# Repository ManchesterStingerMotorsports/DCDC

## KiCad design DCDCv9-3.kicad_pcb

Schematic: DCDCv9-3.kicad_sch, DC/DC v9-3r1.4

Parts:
C1: 2uF; MKP1848520704K2; Mouser Part Number 75-MKP1848520704K2
C2: 2.2uF; C_0805_2012Metric; Manufacturer_Part_Number CL21B225KBYNNWE; not fitted
C3: 22nF; R76UI22205050J; Mouser Part Number 80-R76UI22205050J; not fitted
C4: 3.3nF; C_Disc_D12.5mm_W5.0mm_P10.00mm; Manufacturer_Part_Number VY1332M59Y5UQ63V0
C5, C33, C46: 10uF; C_0805_2012Metric; Manufacturer_Part_Number TMK212BBJ106KG-T
C8, C12, C18, C27, C42, C54: 22uF; C_0805_2012Metric; Manufacturer_Part_Number CL21A226MAYNNNE
C11, C13: 2200uF; CP_Radial_D12.5mm_P5.00mm_symbol_inside; Manufacturer_Part_Number UHW1V222MHD
C14, C28: 100nF; C_0603_1608Metric; Manufacturer_Part_Number HMJ107BB7104KAHT
C15, C40, C41: 2.2uF; C_0805_2012Metric; Manufacturer_Part_Number CL21B225KBYNNWE
C16, C49, C50, C51, C52, C53, C56, C57: 1nF; C_0603_1608Metric; Manufacturer_Part_Number 885342206003
C17, C19, C45: 1uF; C_0603_1608Metric; Manufacturer_Part_Number CL10B105KB8NQNC
C20, C21, C22, C23, C24: 10uF; C_1210_3225Metric; Manufacturer_Part_Number GRM32ER71J106MA12L
C26, C44, C47: 22nF; C_0603_1608Metric; Manufacturer_Part_Number C0603C223K1RAC
C29: 47pF; C_0603_1608Metric; Manufacturer_Part_Number C0603C470J1HACTU
C30, C32, C48: 10nF; C_0603_1608Metric; Manufacturer_Part_Number C0603C103K2RECTU
C34, C35, C36, C37: 5.6nF; C_1210_3225Metric; Manufacturer_Part_Number C1210C562JDGACAUTO
C38: 120pF; C_0603_1608Metric; Manufacturer_Part_Number GCM1885C2A121JA16D; not fitted
C39: 470pF; C_1206_3216Metric; Voltage 400V; Manufacturer_Part_Number 885342208005
C43: 470nF; C_0603_1608Metric; Manufacturer_Part_Number UMK107ABJ474KA-T
C_start1: 3.8V 25F Supercap; CP_Radial_D8.0mm_P3.50mm; Manufacturer_Part_Number VMF256M3R8
D1: HV_Orange; LED_0603_1608Metric_Pad1.05x0.95mm_HandSolder; Manufacturer_Part_Number APTD1608LSECK/J4-PF
D2, D10, D17, D18: 1N4448; D_SOD-123; Manufacturer_Part_Number 1N4448WQ-7-F
D3, D4, D5, D6, D7: Green; LED_0603_1608Metric_Pad1.05x0.95mm_HandSolder; Manufacturer_Part_Number IN-S63AT5G
D8, D15, D16: CDSOD323-T12; D_SOD-323; Manufacturer_Part_Number CDSOD323-T12
D9, D13: SS1H10; D_SMA; Manufacturer_Part_Number SS1H10-M3/61T
D11, D12, D14: VS-E7FX0212-M3/I; D_SMF; Manufacturer_Part_Number VS-E7FX0212-M3/I
F1: 1.6A; Fuseholder0,25Zoll_32mm_littlefuse_102_122; Manufacturer_Part_Number 0ADBC1600-BE
F1.1, F1.2: Manufacturer_Part_Number 01220083Z
F2: 500mA; NANO-0154-OMNI-BLOK-Fuse-Holder; Manufacturer_Part_Number 0154.500DR
F3: 20A; Bel_SMCF_Fuse_2410_6125Metric; Manufacturer_Part_Number 0679L9200-01
J2, J4, J8: Conn_01x02_Male; PinHeader_1x02_P2.54mm_Vertical; Manufacturer_Part_Number 42375-2486
J3, J6, J7: Molex Vert; Molex Microfit Vert
J9: Molex 3 pin; MPN 2165713003
JP1: Fan Voltage Select; SolderJumper-3_P1.3mm_Open_RoundedPad1.0x1.5mm_NumberLabels
L1: 4.7uH; ASPI-4030S; Mouser Part Number ASPI-4030S-4R7M-T
L2: 1uH; 7443091100_v9.2; Manufacturer_Part_Number 7443091100
L3: 10uH; ASPI-4030S; Mouser Part Number 815-ASPI-4030S-100MT
L4, L5, L6, L7, L8, L9, L10, L11: •
M1: Fan; PinHeader_1x02_P2.54mm_Vertical
Q1, Q2, Q5, Q6, Q7: PMV20ENR; SOT-23; Manufacturer_Part_Number PMV20ENR
Q3: SIHP24N80AE-GE3; TO-220-3_Vertical_HV1.2mm; Manufacturer_Part_Number SIHP24N80AE-GE3
Q4: IXYP8N90C3; TO-220-3_Vertical_HV1.2mm; Manufacturer_Part_Number IXYP8N90C3
Q10, Q11: IMBG65R050M2HXTMA1; TO-263-7_TabPin8; Manufacturer_Part_Number IMBG65R050M2HXTMA1
R1, R71: 100M; R_2512_6332Metric_Pad1.40x3.35mm_HandSolder; Manufacturer_Part_Number CHV2512-JW-107ELF
R2, R72: 330k; R_0805_2012Metric; Manufacturer_Part_Number ERJ-P06J334V
R3: 3.0k; R_0603_1608Metric; Manufacturer_Part_Number AF0603JR-073KL; not fitted
R4: 1k; R_0603_1608Metric; Manufacturer_Part_Number ESR03EZPJ102; not fitted
R5, R7, R9, R11, R15, R16, R21, R23, R51, R52, R55, R57, R63: 10k; R_0603_1608Metric; Manufacturer_Part_Number ESR03EZPJ103
R6: 47; R_1206_3216Metric; Manufacturer_Part_Number ERJ-P08J470V
R8, R10, R22, R48, R49: 2.2k; R_0603_1608Metric; Manufacturer_Part_Number ESR03EZPJ222
R12: 910; R_0603_1608Metric; Manufacturer_Part_Number CR0603-FX-9100ELF
R17, R24: 27k; R_0603_1608Metric; Manufacturer_Part_Number CR0603-JW-273ELF
R18, R27, R50: 470k; R_0603_1608Metric; Manufacturer_Part_Number RCS0603470KJNEA
R25: 240k; R_0603_1608Metric; Manufacturer_Part_Number AC0603FR-07240KL
R26, R45, R47, R53, R67, R70, R75: 100k; R_0603_1608Metric; Manufacturer_Part_Number ESR03EZPJ104
R28, R34, R66: 33k; R_0603_1608Metric; Manufacturer_Part_Number AC0603FR-0733KL
R31, R36: 4.7k; R_0603_1608Metric; Manufacturer_Part_Number CRCW06034K70FKEC
R35: 330k; R_0603_1608Metric; Manufacturer_Part_Number AC0603JR-07330KL
R37: 47k; R_0603_1608Metric; Manufacturer_Part_Number RC0603FR-0747KL
R39, R41, R59, R61: 1k; R_0603_1608Metric; Manufacturer_Part_Number ESR03EZPJ102
R44: 510; R_0603_1608Metric; Manufacturer_Part_Number CRCW0603510RFKEBC
R46: 20; R_1206_3216Metric; Manufacturer_Part_Number CR1206-FX-20R0ELF
R54: 10M; R_1206_3216Metric; Manufacturer_Part_Number CHV1206-JW-106ELF
R56, R58: 10; R_1206_3216Metric; Manufacturer_Part_Number RC1206FR-7W10RL
R60: 82k; R_0603_1608Metric; Manufacturer_Part_Number RC0603JR-0782KL
R62, R69: 100M; R_0603_1608Metric; Manufacturer_Part_Number CRCW0603100MJPEAHR
R64: 820k; R_0603_1608Metric; Manufacturer_Part_Number CR0603-FX-8203ELF
R65: 510k; R_0603_1608Metric; Manufacturer_Part_Number CR0603-JW-514ELF
R68: 1.6M; R_0603_1608Metric; Manufacturer_Part_Number AC0603FR-071M6L
R73, R74: 10; R_0603_1608Metric; Manufacturer_Part_Number ERJ-PA3J100V
RV1: 20k; Potentiometer_Bourns_PVG3G; Manufacturer_Part_Number PVG3A203C01R00
RV2: 10k; Potentiometer_Bourns_3214W_Vertical; Manufacturer_Part_Number PVG5A103C03R00
T1: DIY Transformer ETD 39; Transformer_ETD39_uprightV3.6 (PSS 24V); Manufacturer_Part_Number B66363G0000X197
T1.1: Ferrite Core; Manufacturer_Part_Number B66363G0000X197
T1.2: Ferrite Core (gapped); Manufacturer_Part_Number B66363G1000X127
T1.3: 1800 mm 120 x 0.1 mm HF litz wire (Prim); Manufacturer_Part_Number 120 x 0.1 mm
T1.4, T1.5: 165 mm 600 x 0,071 mm HF litz wire (inner Sec); Manufacturer_Part_Number 120 x 0.1 mm
TH1: 3.9k PTC (read build guide!); PinHeader_1x02_P2.54mm_Vertical; Manufacturer_Part_Number TFPTL15L3901FL2B
TH2: 1k PTC; R_0603_1608Metric; Manufacturer_Part_Number TFPT0603L1001DV
U1: RP-1212S; Converter_DCDC_TRACO_TBA 1-1212HI-3kV-iso; Manufacturer_Part_Number RP-1212S
U2: RT9058-90GVL; SOT-23; Manufacturer_Part_Number RT9058-90GVL
U3: MP4541_SOP8-EP; SOIC-8-1EP_3.9x4.9mm_P1.27mm_EP2.29x3mm XL7005; Manufacturer_Part_Number MP4541GN-Z
U4: TLV61048DBVR; SOT-23-6; Manufacturer_Part_Number TLV61048DBVR
U6, U10, U14: LM2904BIDDFR; SOT-23-8_DC-DC_v9; Manufacturer_Part_Number LM2904BIDDFR
U7: TL431BCDBZR; SOT-23; Manufacturer_Part_Number TL431BCDBZRG4
U9: ACPL-217-50AE; SOIC-4_4.55x2.6mm_P1.27mm; Manufacturer_Part_Number ACPL-217-560E
U11: UCC21520DW; SOIC-16W_7.5x10.3mm_P1.27mm; Manufacturer_Part_Number UCC21520DW
U12: UCC25600; SOIC-8_3.9x4.9mm_P1.27mm; Manufacturer_Part_Number UCC25600DR
U13: ZXRE330ASA-7; SOT-23; Manufacturer_Part_Number ZXRE330ASA-7

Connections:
24V_TP: C11.1, C13.1, C50.2, C51.2, C52.2, F2.1, F3.1, J4.1, L2.2, R17.1, R73.1, R74.1
+3V7: C8.1, C54.1, J3.2, JP1.3 (B), L1.1, U4.4 (~SHDN), U4.5 (IN), U4.6 (nc)
+9V: C5.1, C30.2, R39.1, U2.2 (VO), U9.1
+12V_HS: C41.2, D14.1 (K), U11.16 (VDDA)
+12V_IN: C2.2, C40.2, C45.2, C46.1, D2.1 (K), D3.2 (A), D4.2 (A), D11.1 (K), R70.1, U11.3 (VCCI), U11.8 (VCCI), U11.11 (VDDB), U12.7 (VCC), U14.8 (V+)
+12V_sw: C18.1, C19.2, C27.1, D9.1 (K), J8.1, JP1.1 (A), R16.1, R21.2, R27.1, R34.1, R35.2, R36.2, U1.1 (+VIN), U2.3 (VI), U6.8 (V+); also elsewhere on the board
+24V: C15.2, C53.2, F2.2, R26.2, U3.1 (EN), U3.8 (VIN)
+HV: C1.2, C34.1, C35.1, F1.2, Q11.8 (D), R1.1, R71.1, R72.1
+HV_in: F1.1, J9.3
-HV_in: C33.2, C38.1, D13.1 (K), J9.1, Q3.3 (S), R6.2, R7.2, R48.1, R50.1, R51.2, U1.5 (-VOUT), U10.4 (V-)
-HV_pc: C1.1, C3.2 (2_2), C4.1, C32.2, C36.2, C37.2, C43.2, C44.1, C45.1, C46.2, C47.2, D12.1 (K), D18.2 (A), Q1.2 (S), Q2.2 (S), Q3.2 (D), Q4.2 (C), Q10.3 (S), Q10.4 (S), Q10.5 (S), Q10.6 (S), Q10.7 (S), R2.2, R3.2, R5.1, R59.2, R60.1, R65.2, R68.2, RV1.3, RV2.2, RV2.3, U9.3, U11.4 (GND), U11.5 (DIS), U11.6 (DT), U12.6 (GND), U13.2, U14.4 (V-)
/HB_out: Q10.8 (D), Q11.3 (S), Q11.4 (S), Q11.5 (S), Q11.6 (S), Q11.7 (S), T1.1 (AA)
/HS: U11.1 (INA), U12.8 (GD1)
/LS: U11.2 (INB), U12.5 (GD2)
/OC: C44.2, D17.1 (K), R60.2, U12.3 (OC)
/OTP_FAN: Q5.1 (G), R18.1, U6.7
/OTP_OFF: D10.1 (K), Q6.1 (G), U6.1
/OVP: Q2.1 (G), R69.1, U14.7
/Opc+: C32.1, R44.2, U9.4
/Synchronous Rectification/3: T1.3 (SB); also elsewhere on the board
/Synchronous Rectification/5: T1.5 (SA); also elsewhere on the board
/UVP: Q1.1 (G), R62.1, R63.1, U14.1
GND: C4.2, C5.2, C8.2, C11.2, C12.1, C13.2, C15.1, C17.1, C18.2, C20.2, C21.2, C22.2, C23.2, C24.2, C27.2, C28.1, C48.1, C49.1, C50.1, C51.1, C52.1, C53.1, C54.2, C56.1, C57.1, C_start1.2 (-), D6.1 (K), D8.2 (A2), J4.2, J7.1, J7.2, Q5.2 (S), Q6.2 (S), R10.2, R11.2, R15.1, R22.1, R23.2, R25.1, R28.2, R31.1, R75.2, TH2.2, U2.1 (GND), U3.7 (GND), U4.2 (GND), U6.4 (V-), U7.3 (A); also elsewhere on the board
unnamed: C2.1, R4.2
unnamed: C26.2, R37.1
unnamed: C30.1, R41.1, U9.2
unnamed: C39.2, R54.1
unnamed: C42.2, R59.1
unnamed: C49.2, F3.2, J6.1, J6.2
unnamed: C56.2, R73.2
unnamed: C57.2, R74.2
unnamed: C_start1.1 (+), J3.1, Q7.3 (D)
unnamed: D1.2 (A), R72.2
unnamed: D1.1 (K), R2.1
unnamed: C47.1, D2.2 (A), R67.2, R71.2, U14.2 (-)
unnamed: D3.1 (K), R63.2
unnamed: D4.1 (K), R5.2
unnamed: D5.2 (A), R9.1
unnamed: D5.1 (K), R7.1, R8.2, U10.7
unnamed: D6.2 (A), R21.1
unnamed: C12.2, C16.2, D7.2 (A), L3.2, Q7.2 (S), R24.1
unnamed: D7.1 (K), R22.2
unnamed: D8.1 (A1), Q7.1 (G), R26.1
unnamed: D9.2 (A), L1.2, U4.1 (SW)
unnamed: C48.2, D10.2 (A), R11.1, R34.2, U6.3 (+)
unnamed: C33.1, D11.2 (A), R9.2, R45.2, R46.2, R47.2, R53.2, U1.7 (+VOUT), U10.8 (V+)
unnamed: D12.2 (A), R52.1
unnamed: D13.2 (A), Q4.3 (E), R6.1, U10.2 (-)
unnamed: D14.2 (A), R46.1
unnamed: D15.1 (A1), Q10.1 (G), R55.1, R56.1
unnamed: C40.1, D15.2 (A2), Q10.2 (DS), R55.2, U11.9 (VSSB)
unnamed: D16.1 (A1), Q11.1 (G), R57.1, R58.1
unnamed: C41.1, D16.2 (A2), Q11.2 (DS), R57.2, U11.14 (VSSA)
unnamed: C39.1, D17.2 (A), D18.1 (K)
unnamed: J2.1, JP1.2 (C)
unnamed: J2.2, Q5.3 (D)
unnamed: C19.1, J8.2, R31.2, R75.1, U6.6 (-)
unnamed: L4.2, L5.1
unnamed: L6.1, L7.2
unnamed: L8.1, L9.1
unnamed: L10.1, L11.2
unnamed: Q1.3 (D), Q2.3 (D), R61.1
unnamed: Q3.1 (G), R8.1
unnamed: Q4.1 (G), R49.1
unnamed: R10.1, R12.2
unnamed: R49.2, R51.1, U10.1
unnamed: R65.1, R66.2
unnamed: R67.1, R68.1
unnamed: C34.2, C35.2, C36.1, C37.1, R54.2, T1.2 (AB)
unnamed: C20.1, C21.1, C22.1, C23.1, C24.1, L2.1, T1.4 (SC)
unnamed: C14.2, U3.5 (BST)
unnamed: C16.1, R23.1, R24.2, U3.4 (FB)
unnamed: R25.2, U3.3 (FREQU)
unnamed: C14.1, L3.1, U3.6 (SW)
unnamed: C17.2, U3.2 (VCC)
unnamed: R27.2, R28.1, U4.3 (FB)
unnamed: C28.2, R35.1, R36.1, TH2.1, U6.2 (-)
unnamed: R15.2, R16.2, R18.2, U6.5 (+)
unnamed: C29.2, R37.2, R39.2, R41.2, U7.1 (K)
unnamed: C26.1, C29.1, R12.1, R17.2, U7.2 (REF)
unnamed: R45.1, R48.2, U10.3 (+)
unnamed: R47.1, R50.2, U10.5 (+)
unnamed: C38.2, R52.2, R53.1, U10.6 (-)
unnamed: R58.2, U11.15 (OUTA)
unnamed: R56.2, U11.10 (OUTB)
unnamed: R3.1, R4.1, RV1.1, RV1.2, U12.1 (DT)
unnamed: C42.1, R44.1, RV2.1, U12.2 (RT)
unnamed: C43.1, R61.2, U12.4 (SS)
unnamed: R62.2, R64.1, U14.3 (+)
unnamed: R1.2, R66.1, R69.2, U14.5 (+)
unnamed: R64.2, R70.2, U13.1, U14.6 (-)
OTP_FET: Q6.3 (D), U1.2 (-VIN)

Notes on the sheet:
2.79V
PWM ramp-up hack via dead time (not working!) when C2+R4 is installed with 10 uF and 1k somehow the soft start does not work properly. It starts from 127 kHz and goes down to 95 kHz (normal). When C2 is not installed, Soft start starts from 341 kHz (nice!)
3.3 V (constant)
f_max
OVP Voltages: 100 Meg + 543 k Measured 241127: Enable: 609V / Disable 598V -> OK
Calculation is not up-to date, as R75 (100k) was added on 250619 R54 = 470k U_on = 5.9466 V = 4784.4 Ω = 1.2267 = 77 °C U_off = 6.0533 V = 4617.2 Ω = 1.1839 = 68 °C 106.7 mV hysteresis
between 2.5V and 3.8V (depending on SOC) ESR: 0,65 Ω (DC), 0,3Ω (1kHz AC)
If the MP4541 is not available, use the MP4581 (1:1 compatible, 100V variant)
500mW
FB Voltage: 1.0 V V_out = 1.0 * (1+ R_24/R_23) V_out = 1.0 * (1+ 27k/10k) = 3.7 V Note: 3.7 V is used for some safty margin to the allowed 3.8 V of the Supercap.
HV DC in
UVP
Cr_B
CC precharge IGBT
C3 is a hidden footprint for a film capacitor on the PCB as backup solution in case of a Cr_A / Cr_B failure. If needed, pin 1 must be connected with a short cable to T1 pin 2. If C3 is used, P_out must not exceed 500W !
Lp = 166 µH Lr = 56 µH
The UVP/OVP signals pull down the soft start capacitor, and force the UCC25600 to turn off. When UVP/OVP are OK (low), the soft start capacitor is recharged, while a sweep from high frequency to lower (normal) frequency is output, resulting in a soft start of the half-bridge. RT is also LOW when SS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
470 nF - UCC25600 Tool Softstart: 265ms
R_dT
f_min
precharge-close MOS
Placed near U2
SOT23-5 Footprint was adapted to SOT23-6 (mostly cross compatible) Works for: - TLV61048DBVR, 3.7 A, FB-Voltage: 0.8 V (best efficieny), 600 kHz, 2 ms softstart, U_in_min 2.65 (RECOMMENDED, USED HERE) - MT3608, 2 A, FB-Voltage: 0.6 V (often found in cheap Amazon Boost converters), 1200 kHz, U_in_mi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
Mount TH1 on the outsiede of the transformer. NOT INSIDE FOOTPRINT J8!
local bypass for U12
Glossary OCP over current protection UVP under voltage protectin PC precharge ref reference (voltage) sw manually switched switch/connector/source HV high voltage opc optocoupler opamp operational amplifier pwr power dashed line modul/sub module dash-dotted line optional part, see comment
DC/DC enable Switch
TH2 is next to SR FETs
OVP
p_max = 3.3 W @ 600 V
Split resonant capacitors result in half the Current per cap and a DC_link_cap capacity reduction by appx. 3.5x (same Voltage ripple). Not more than 2 Arms per side are expected at 400V / 500W load. However, it's better having 2 in parallel, bc I dont like seeing burning C0G caps (again).
2.5*(1+((27)/(2.2+0.91))) = 24.2042 V
Overtemperature Protection and Fan control
current sensing shunt I_pc = 5.5 mA
|__________| = 4634.0 Ω
V_curr_sens
V_ref = 258 mV
11.7k = 300ns
Active Center tapped Full-Wave Rectifier
UCC21520 A bypass capacitor connected to VCCI supports the transient current needed for the primary logic and the total current consumption, which is only a few mA. Therefore, a 50-V MLCC with over 100 nF is recommended for this application. -> See Datasheet for further information

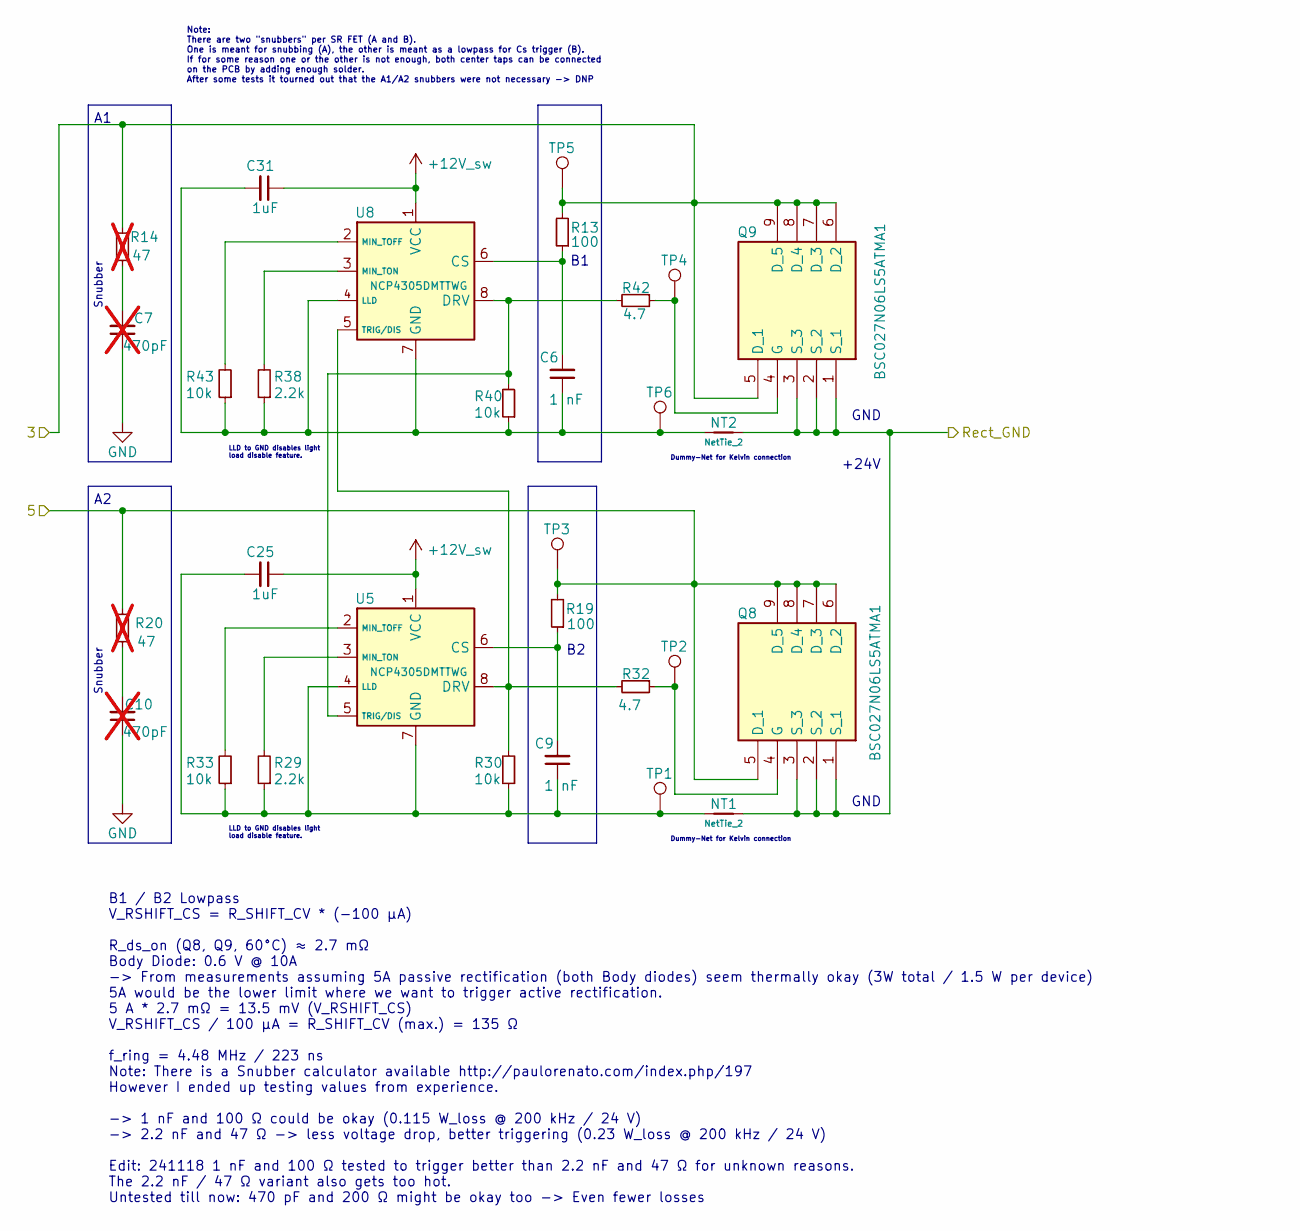
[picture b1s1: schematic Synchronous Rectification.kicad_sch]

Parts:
C6, C9: 1 nF; C_1206_3216Metric; Manufacturer_Part_Number SH31B102K631CT
C7, C10: 470pF; C_1206_3216Metric; Manufacturer_Part_Number 885342208005; not fitted
C25, C31: 1uF; C_0603_1608Metric; Manufacturer_Part_Number CL10B105KB8NQNC
NT1, NT2: NetTie_2; dummy_net_line_0.5mm
Q8, Q9: BSC027N06LS5ATMA1; Mouser Part Number 726-BSC027N06LS5ATMA
R13, R19: 100; R_1206_3216Metric; Manufacturer_Part_Number RC1206JR-7W100RL
R14, R20: 47; R_1206_3216Metric; Manufacturer_Part_Number ERJ-P08J470V; not fitted
R29, R38: 2.2k; R_0603_1608Metric; Manufacturer_Part_Number ESR03EZPJ222
R30, R33, R40, R43: 10k; R_0603_1608Metric; Manufacturer_Part_Number ESR03EZPJ103
R32, R42: 4.7; R_1206_3216Metric; Manufacturer_Part_Number ERJ-P08J4R7V
TP1, TP2, TP3, TP4, TP5, TP6: TestPoint; TestPoint_Pad_D0.8mm_DC-DC
U5, U8: NCP4305DMTTWG; WDFN-8_2x2mm_P0.5mm; Manufacturer_Part_Number NCP4305DMTTWG

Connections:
+12V_sw: C25.1, C31.1, U5.1 (VCC), U8.1 (VCC); also elsewhere on the board
/Synchronous Rectification/3: Q9.5 (D_1), Q9.6 (D_2), Q9.7 (D_3), Q9.8 (D_4), Q9.9 (D_5), R13.2, R14.1, TP5.1 (1_1); also elsewhere on the board
/Synchronous Rectification/5: Q8.5 (D_1), Q8.6 (D_2), Q8.7 (D_3), Q8.8 (D_4), Q8.9 (D_5), R19.2, R20.1, TP3.1 (1_1); also elsewhere on the board
GND: C7.1, C10.1, NT1.2, NT2.2, Q8.1 (S_1), Q8.2 (S_2), Q8.3 (S_3), Q9.1 (S_1), Q9.2 (S_2), Q9.3 (S_3); also elsewhere on the board
unnamed: C7.2, R14.2
unnamed: C10.2, R20.2
unnamed: Q8.4 (G), R32.1, TP2.1 (1_1)
unnamed: Q9.4 (G), R42.1, TP4.1 (1_1)
unnamed: C9.2, R19.1, U5.6 (CS)
unnamed: R30.2, R32.2, U5.8 (DRV), U8.5 (TRIG/DIS)
unnamed: C9.1, C25.2, NT1.1, R29.1, R30.1, R33.1, TP1.1 (1_1), U5.4 (LLD), U5.7 (GND)
unnamed: R33.2, U5.2 (MIN_TOFF)
unnamed: R29.2, U5.3 (MIN_TON)
unnamed: R40.2, R42.2, U5.5 (TRIG/DIS), U8.8 (DRV)
unnamed: C6.2, R13.1, U8.6 (CS)
unnamed: C6.1, C31.2, NT2.1, R38.1, R40.1, R43.1, TP6.1 (1_1), U8.4 (LLD), U8.7 (GND)
unnamed: R43.2, U8.2 (MIN_TOFF)
unnamed: R38.2, U8.3 (MIN_TON)

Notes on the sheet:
GND
LLD to GND disables light load disable feature.
B1 / B2 Lowpass V_RSHIFT_CS = R_SHIFT_CV * (-100 µA) R_ds_on (Q8, Q9, 60°C) ≈ 2.7 mΩ Body Diode: 0.6 V @ 10A -> From measurements assuming 5A passive rectification (both Body diodes) seem thermally okay (3W total / 1.5 W per device) 5A would be the lower limit where we want to trigger active rectif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
+24V
Snubber
Dummy-Net for Kelvin connection
Note: There are two "snubbers" per SR FET (A and B). One is meant for snubbing (A), the other is meant as a lowpass for Cs trigger (B). If for some reason one or the other is not enough, both center taps can be connected on the PCB by adding enough solder. After some tests it tourned out that the A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

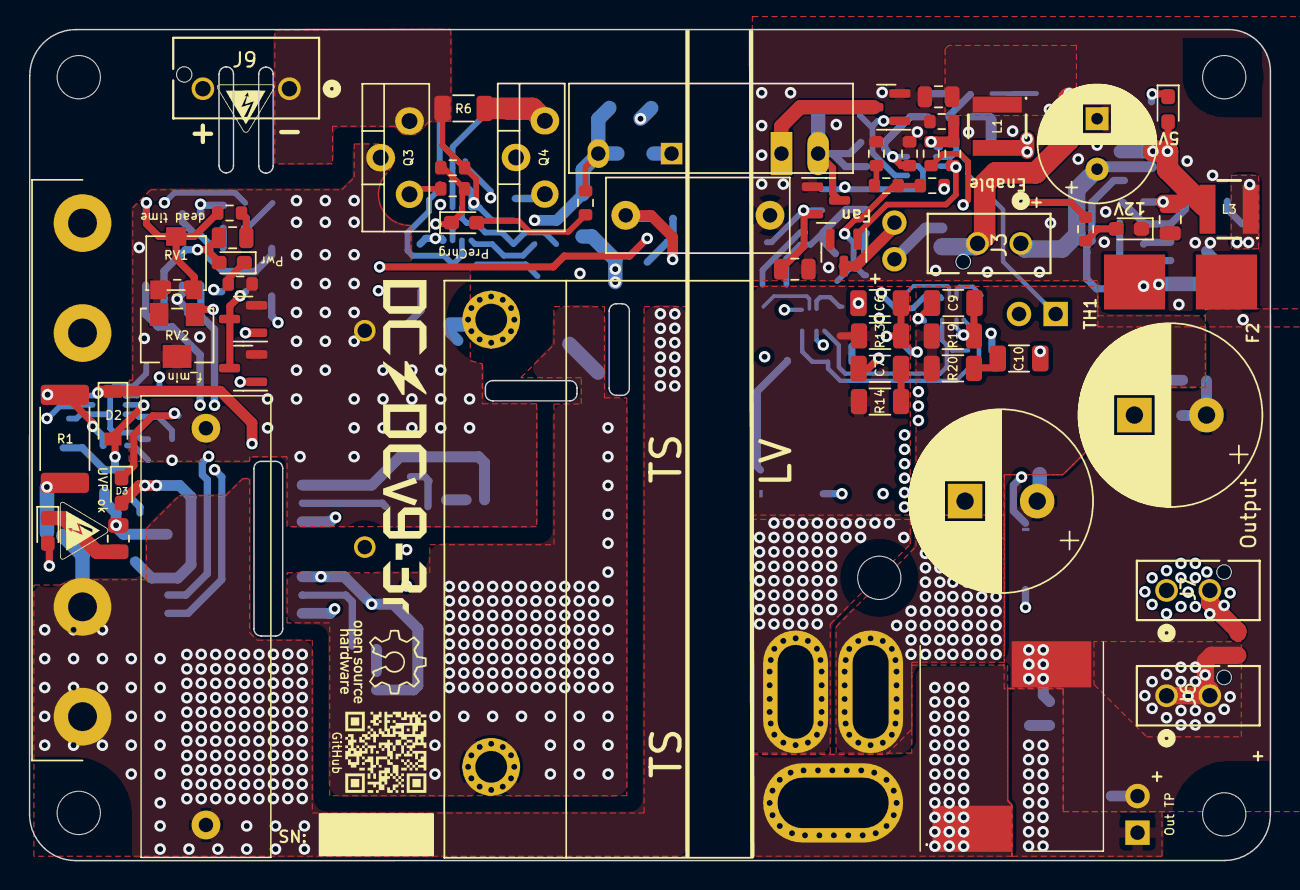
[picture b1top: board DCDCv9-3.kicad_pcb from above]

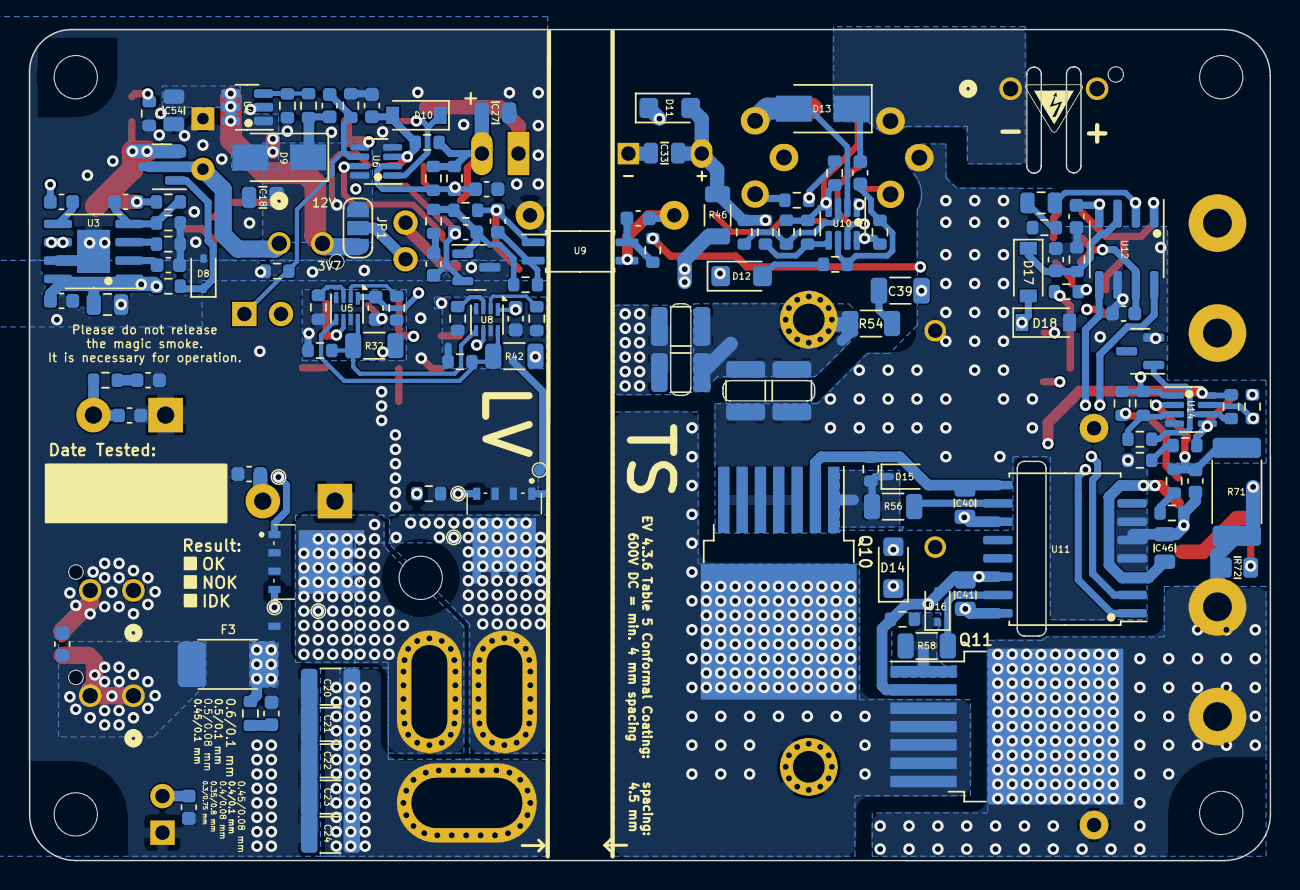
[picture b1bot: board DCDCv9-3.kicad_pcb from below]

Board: 4 copper layers, 86.0 x 57.6 mm, 206 parts (138 on the bottom side), 102 nets.

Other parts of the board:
HV_Logo_1, HV_Logo_1#2, HV_Logo_1#3: HV_Logo_1; HV_Logo_small
QR_Coode_1: QR_Coode; GitHub_QR_Code
TP8: GaN GND2; TestPoint_Pad_D0.8mm_DC-DC

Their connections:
GND: TP8.1; also elsewhere on the board

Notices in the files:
DCDCv9-3.kicad_sch:
under the CERN-OHL-W license
